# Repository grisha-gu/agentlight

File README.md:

# AgentLight

An open-source USB desk indicator for [Claude Code](https://code.claude.com) agents.
Four columns of traffic lights show what each running agent is doing; the button under
a column brings that agent's terminal tab to the front.

```
         ╱───────────────────────────────╲
        ╱   ●     ●     ●     ●           ╲   red    — needs your input
       ╱    ●     ●     ●     ●            ╲  yellow — working
      ╱     ●     ●     ●     ●             ╲ green  — done, ready for input
     ╱    ┌───┐ ┌───┐ ┌───┐ ┌───┐            ╲
    ╱     │ 1 │ │ 2 │ │ 3 │ │ 4 │             ╲ button — focus the agent's terminal
   ╱      └───┘ └───┘ └───┘ └───┘              ╲
  └────────────────────────────────────────────┘
```

A flat box about 97 × 97 mm with a 4 × 4 grid, like a stream deck. It connects to a Mac
over USB-C; everything sits on a single PCB built around an RP2040.

The project has three parts, all in this repository:

* **hardware** — a two-layer PCB (KiCad) with 12 through-hole LEDs, 4 MX key switches
  in hot-swap sockets and a Waveshare RP2040-Zero module; a 3D-printed enclosure;
* **firmware** — C on the Raspberry Pi Pico SDK + TinyUSB: a composite vendor HID +
  CDC device;
* **host** — a macOS menu bar app and CLI in Swift that receives Claude Code hooks and
  drives the device. It also works without the device: the same lights are shown in
  the menu bar.

## States

| Agent state | Light | Claude Code hook events |
|---|---|---|
| thinking / running tools | 🟡 yellow | `UserPromptSubmit`, `PreToolUse`, `PostToolUse` |
| needs input (permission, question) | 🔴 red | `PermissionRequest`, `Notification(permission_prompt / agent_needs_input)`, `Elicitation` |
| idle, ready for input | 🟢 green | `Stop`, `Notification(agent_completed)` |
| not connected | ⚫ off | `SessionEnd`, timeout, daemon gone |
| connected | welcome animation | `SessionStart` |

## How it works

```
┌──────────────────────┐
│  Claude Code #1..#N  │  hooks (http + command)
└──────────┬───────────┘
           │ POST http://127.0.0.1:48879/hook
┌──────────▼───────────────────────────────────┐
│  agentlightd  (Swift, LaunchAgent)           │
│   • HTTP server for hooks                    │
│   • slot allocator: session_id → slot 0..N-1 │
│   • state machine per slot                   │
│   • terminal tab focus (AppleScript)         │
└──────────┬───────────────────────────────────┘
           │ USB: vendor HID reports (+ CDC for logs)
┌──────────▼───────────────────────────────────┐
│  RP2040 firmware                             │
│   • 12 LEDs (4 × R/Y/G), 14-bit PWM          │
│   • 4 buttons, debounce                      │
│   • animations, gamma, colour calibration    │
│   • watchdog: no heartbeat → all lights off  │
└──────────────────────────────────────────────┘
```

## Getting started

Install the macOS app:

```bash
brew install --cask grisha-gu/tap/agentlight
agentlight install-daemon      # start at login
agentlight install-hooks       # add hooks to ~/.claude/settings.json (existing hooks are kept)
agentlight doctor
```

Then start `claude` in Terminal.app: the menu bar shows its light. With the device
plugged in, the same state appears on the device.

To build the device, start with [docs/06-assembly.md](docs/06-assembly.md).

## Documentation

| File | Contents |
|---|---|
| [docs/01-architecture.md](docs/01-architecture.md) | state machine, hook mapping, slot allocation |
| [docs/02-hardware.md](docs/02-hardware.md) | parts, schematic, pinout, PCB, BOM, enclosure |
| [docs/03-protocol.md](docs/03-protocol.md) | USB protocol between the host and the device |
| [docs/04-firmware.md](docs/04-firmware.md) | firmware structure, animations, building and flashing |
| [docs/05-host-macos.md](docs/05-host-macos.md) | daemon, hook installation, terminal focus, launchd |
| [docs/06-assembly.md](docs/06-assembly.md) | ordering the board, assembly, troubleshooting |
| [host/README.md](host/README.md) | building and installing the macOS app |
| [hardware/pcb/README.md](hardware/pcb/README.md) | generating the PCB; [ORDER.md](hardware/pcb/ORDER.md) — ordering from JLCPCB |

## Repository layout

```
firmware/            RP2040 firmware (C, Pico SDK)
host/                macOS daemon, menu bar app and CLI (Swift)
hardware/pcb/        KiCad PCB and the scripts that generate it
packaging/homebrew/  Homebrew cask
tools/               protocol test, flashing script, hook capture
docs/                design documentation
```

## Status

| Part | Status |
|---|---|
| Firmware | 0.6.0, tested on a breadboard prototype |
| macOS app | 0.3.1, released (Homebrew, signed and notarized) |
| PCB | rev. a, ordered |
| Enclosure | in design |

## USB identifiers

The device enumerates as a composite device (vendor-defined HID, usage page `0xFF00`,
plus CDC-ACM) with the manufacturer and product string `AgentLight`. During
development it uses the Pico SDK default VID:PID `2E8A:000A`; a dedicated PID under
the [pid.codes](https://pid.codes) VID `0x1209` will replace it.

## License

* Software (`firmware/`, `host/`, `tools/`, `packaging/`) — [MIT](LICENSE).
* Hardware (`hardware/`) — [CERN-OHL-P-2.0](hardware/LICENSE).
* Documentation (`docs/`) — [CC-BY-4.0](docs/LICENSE).

Third-party: the Kailh hot-swap footprint is adapted from
[ebastler/marbastlib](https://github.com/ebastler/marbastlib) (CERN-OHL-P-2.0);
`firmware/pico_sdk_import.cmake` comes from the Raspberry Pi Pico SDK (BSD-3-Clause).

AgentLight is an independent project and is not affiliated with Anthropic.

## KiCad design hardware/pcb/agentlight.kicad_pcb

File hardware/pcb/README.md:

# AgentLight PCB rev. a

The board is generated entirely by scripts — edit them, not `agentlight.kicad_pcb`
(the next build overwrites it). Circuit and parts:
[docs/02-hardware.md](../../docs/02-hardware.md).

Licensed under [CERN-OHL-P-2.0](../LICENSE).

```sh
./build.sh      # generate + route → DRC → build/jlc/ (Gerber zip, BOM, CPL) + renders + 1:1 PDFs
```

| File | What it does |
|---|---|
| `gen_board.py` | geometry (20.32 mm grid, 91 × 91 mm board), parts, nets, **tracks**, outline, mounting holes, GND pour, design rules |
| `gen_module_fp.py` | RP2040-Zero pin map and outline footprint (2 × 9 side pins + 5 on the bottom edge) |
| `drc.sh` | DRC summary, silkscreen checks excluded |
| `fab.py` | JLCPCB outputs: Gerbers + drill, BOM and CPL for the back side |
| `agentlight.pretty/` | custom footprints; the Kailh hot-swap footprint is adapted from [ebastler/marbastlib](https://github.com/ebastler/marbastlib) (CERN-OHL-P-2.0) |

Requires KiCad 10 (the scripts run with KiCad's bundled Python, `pcbnew` API).

Routing is deterministic and done by the script, not an autorouter: the bus runs as
horizontal tracks on the front side below the module; each slot has a vertical lane on
the back side to the right of its column, with short stubs to the resistors; all corners
are 45°. Details are in the comments in `gen_board.py`.

Ordering: [ORDER.md](ORDER.md).

Hand-assembled (not in the factory BOM/CPL): 12 LEDs, the module itself, mounting
hardware. The module sockets J1–J3 are through-hole parts placed by the factory
(Hong Cheng HC-PM254-5.0H, 5 mm low profile).

Expected DRC warnings:

* J1–J3 corners (`courtyards_overlap`): the bottom socket butts against the side ones,
  as the RP2040-Zero pinout requires;
* `isolated_copper`: narrow pour slivers between bus tracks, kept to avoid voids.

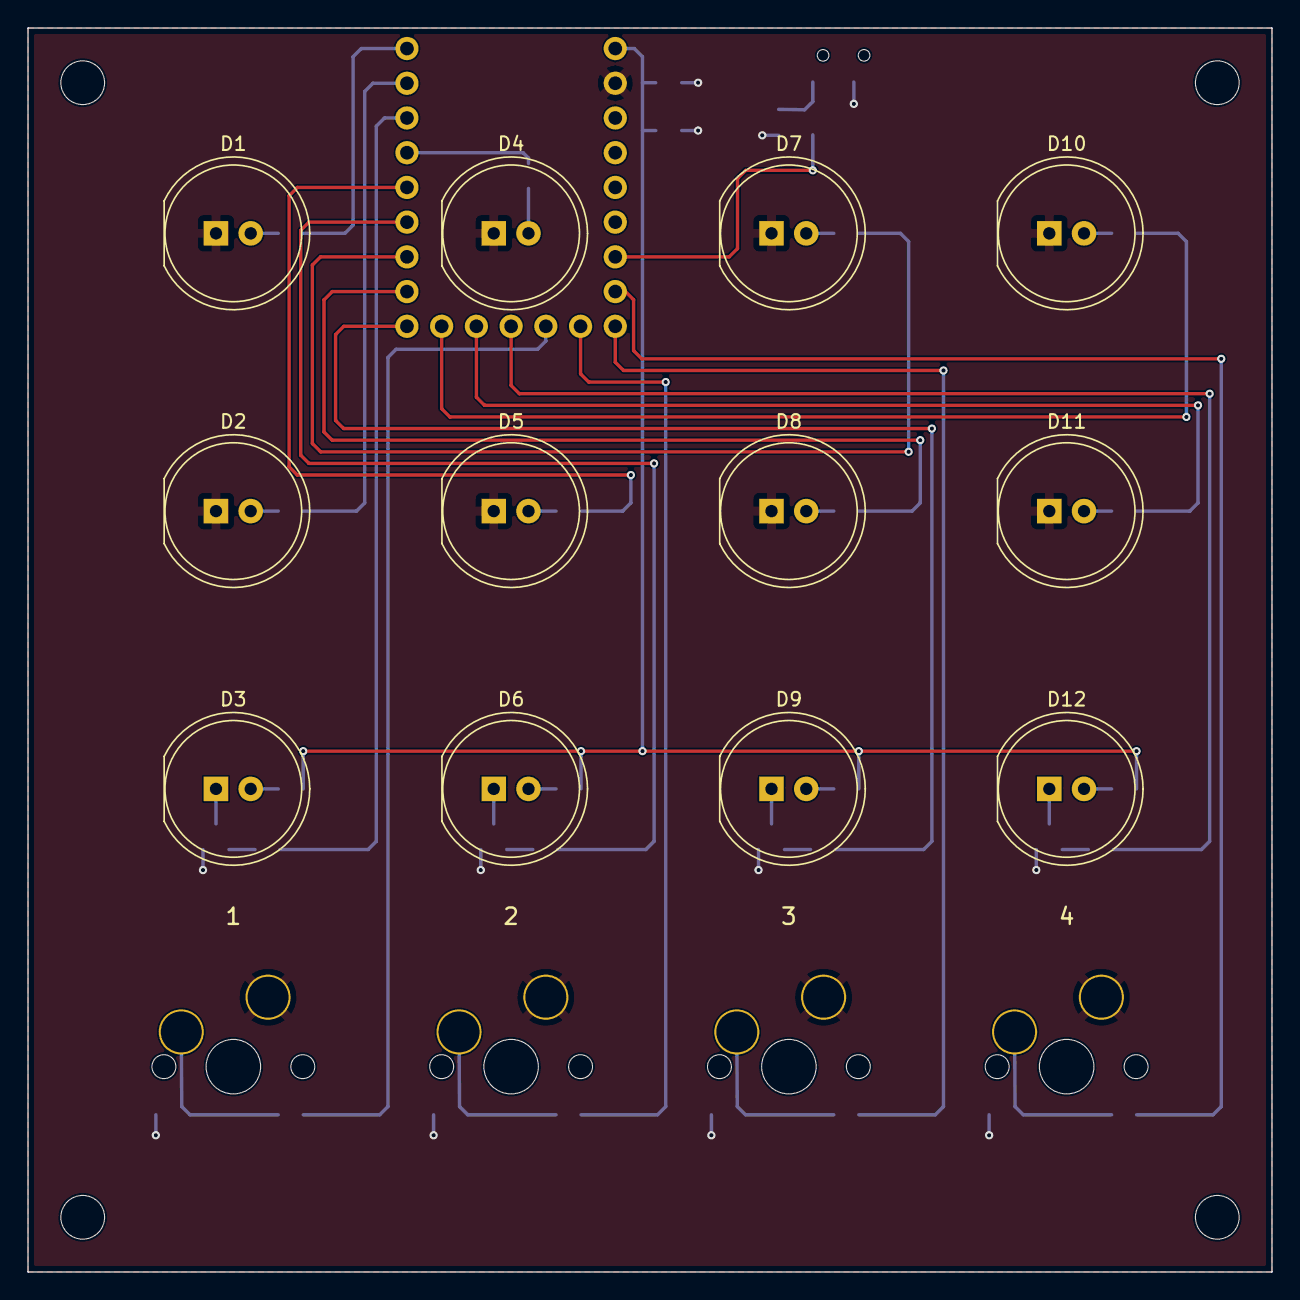
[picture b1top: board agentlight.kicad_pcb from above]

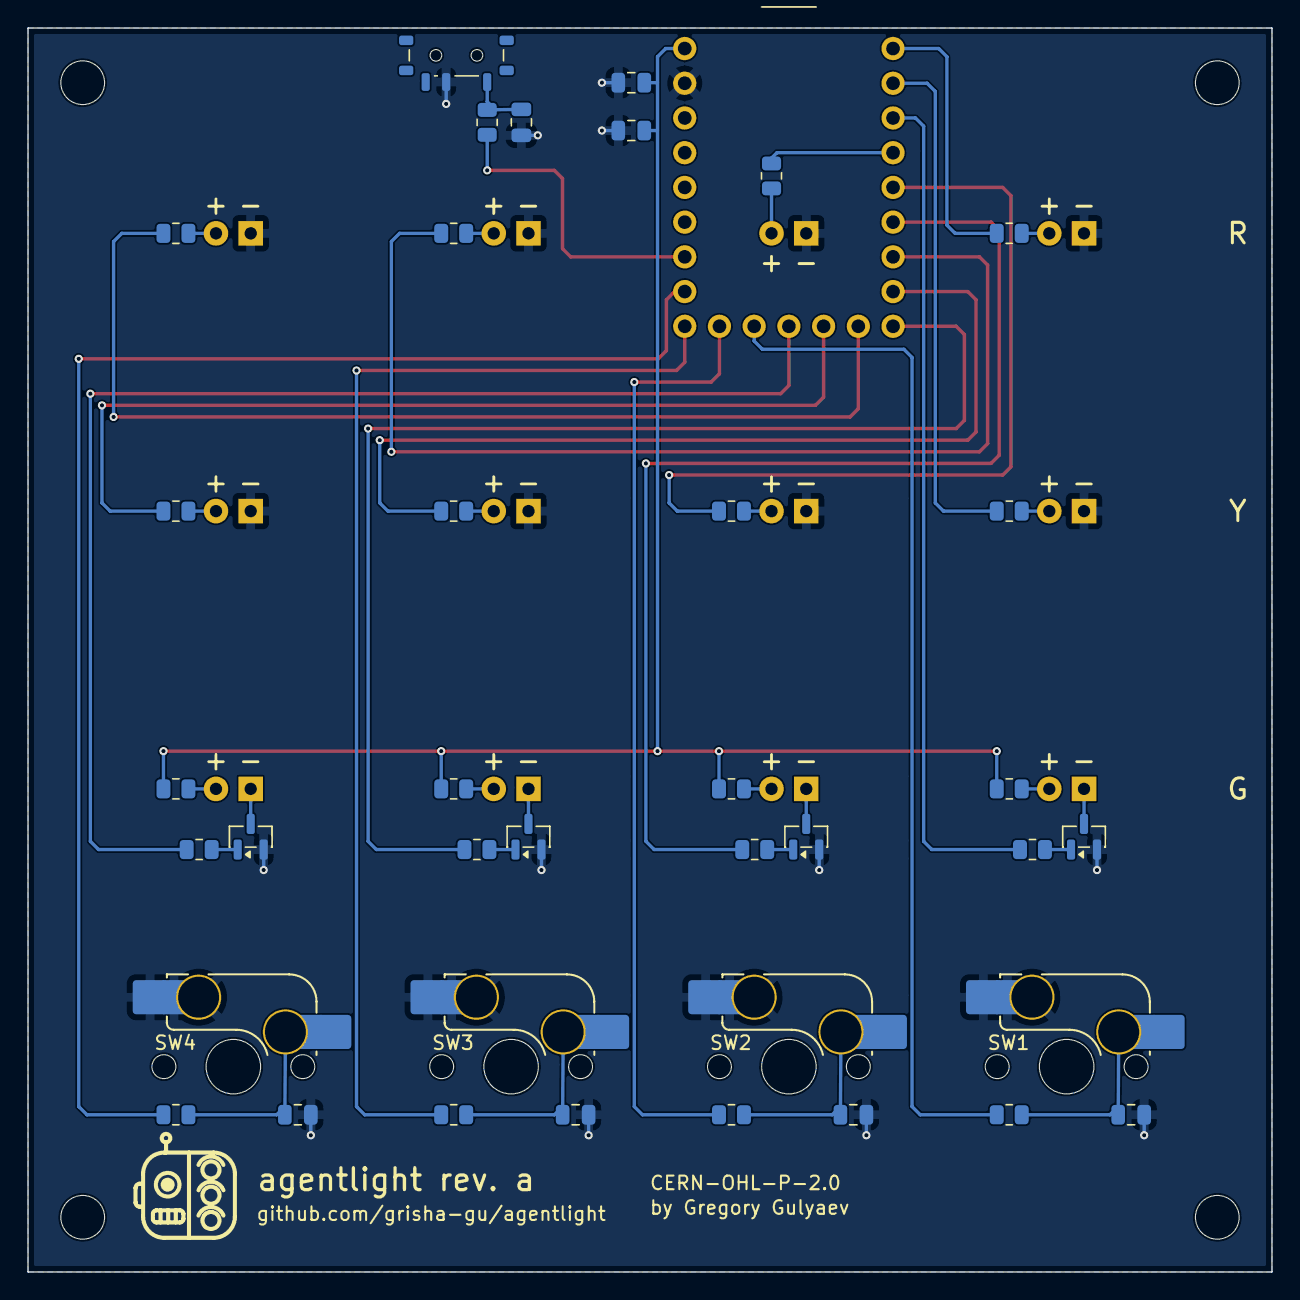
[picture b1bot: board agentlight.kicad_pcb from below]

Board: 2 copper layers, 91.0 x 91.0 mm, 57 parts (41 on the bottom side), 44 nets.

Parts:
C1, C2, C3, C4, C5, C7: 100n; C_0805_2012Metric
C6: 10u; C_0805_2012Metric
D1, D4, D7, D10: LED10_RED; LED_D10.0mm
D2, D5, D8, D11: LED10_YELLOW; LED_D10.0mm
D3, D6, D9, D12: LED10_GREEN; LED_D10.0mm
H1, H2, H3, H4: M3; MountingHole_3.2mm_M3
J1, J2: Socket_1x8; PinSocket_1x08_P2.54mm_Vertical
J3: Socket_1x7; PinSocket_1x07_P2.54mm_Vertical
Q1, Q2, Q3, Q4: S8050; SOT-23
R1, R2, R4, R5, R7, R8, R10, R11, R31, R32, R33, R34, R35: 220; R_0805_2012Metric
R3, R6, R9, R12: 330; R_0805_2012Metric
R21, R22, R23, R24: 1k; R_0805_2012Metric
SW1, SW2, SW3, SW4: MX_hotswap; SW_MX_HS_CPG151101S11_1u
SW5: MSK12C02; SW_SPDT_Shouhan_MSK12C02
U1: RP2040-Zero; RP2040-Zero_Outline

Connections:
+5V: C6.2, C7.2, J2.1, R3.1, R6.1, R9.1, R12.1
BTN0: C1.1, R31.2, SW1.1
BTN1: C2.1, R32.2, SW2.1
BTN2: C3.1, R33.2, SW3.1
BTN3: C4.1, R34.2, SW4.1
GND: C1.2, C2.2, C3.2, C4.2, C5.1, C6.1, C7.1, D1.1, D2.1, D4.1, D5.1, D7.1, D8.1, D10.1, D11.1, J2.2, Q1.2, Q2.2, Q3.2, Q4.2, SW1.2, SW2.2, SW3.2, SW4.2, SW5.2
GP0: J1.1, R1.1
GP1: J1.2, R2.1
GP2: J1.3, R21.1
GP3: J1.4, R4.2
GP4: J1.5, R5.1
GP5: J1.6, R22.1
GP6: J1.7, R7.1
GP7: J1.8, R8.1
GP8: J3.1, R23.1
GP9: J3.2, R10.1
GP10: J3.3, R11.1
GP11: J3.4, R24.1
GP12: J3.5, R31.1
GP13: J3.6, R32.1
GP14: J3.7, R33.1
GP15: J2.8, R34.1
GP26: J2.7, R35.1
LED0_A: D1.2, R1.2
LED1_A: D2.2, R2.2
LED2_A: D3.2, R3.2
LED2_K: D3.1, Q1.3
LED3_A: D4.2, R4.1
LED4_A: D5.2, R5.2
LED5_A: D6.2, R6.2
LED5_K: D6.1, Q2.3
LED6_A: D7.2, R7.2
LED7_A: D8.2, R8.2
LED8_A: D9.2, R9.2
LED8_K: D9.1, Q3.3
LED9_A: D10.2, R10.2
LED10_A: D11.2, R11.2
LED11_A: D12.2, R12.2
LED11_K: D12.1, Q4.3
PWR_SW: C5.2, R35.2, SW5.1
Q0_B: Q1.1, R21.2
Q1_B: Q2.1, R22.2
Q2_B: Q3.1, R23.2
Q3_B: Q4.1, R24.2

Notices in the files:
parts and their libraries:
Footprint for Cherry MX style switches with Kailh hotswap socket. From ebastler/marbastlib (CERN-OHL-P-2.0). Drawn mirrored: place flipped on B.Cu
